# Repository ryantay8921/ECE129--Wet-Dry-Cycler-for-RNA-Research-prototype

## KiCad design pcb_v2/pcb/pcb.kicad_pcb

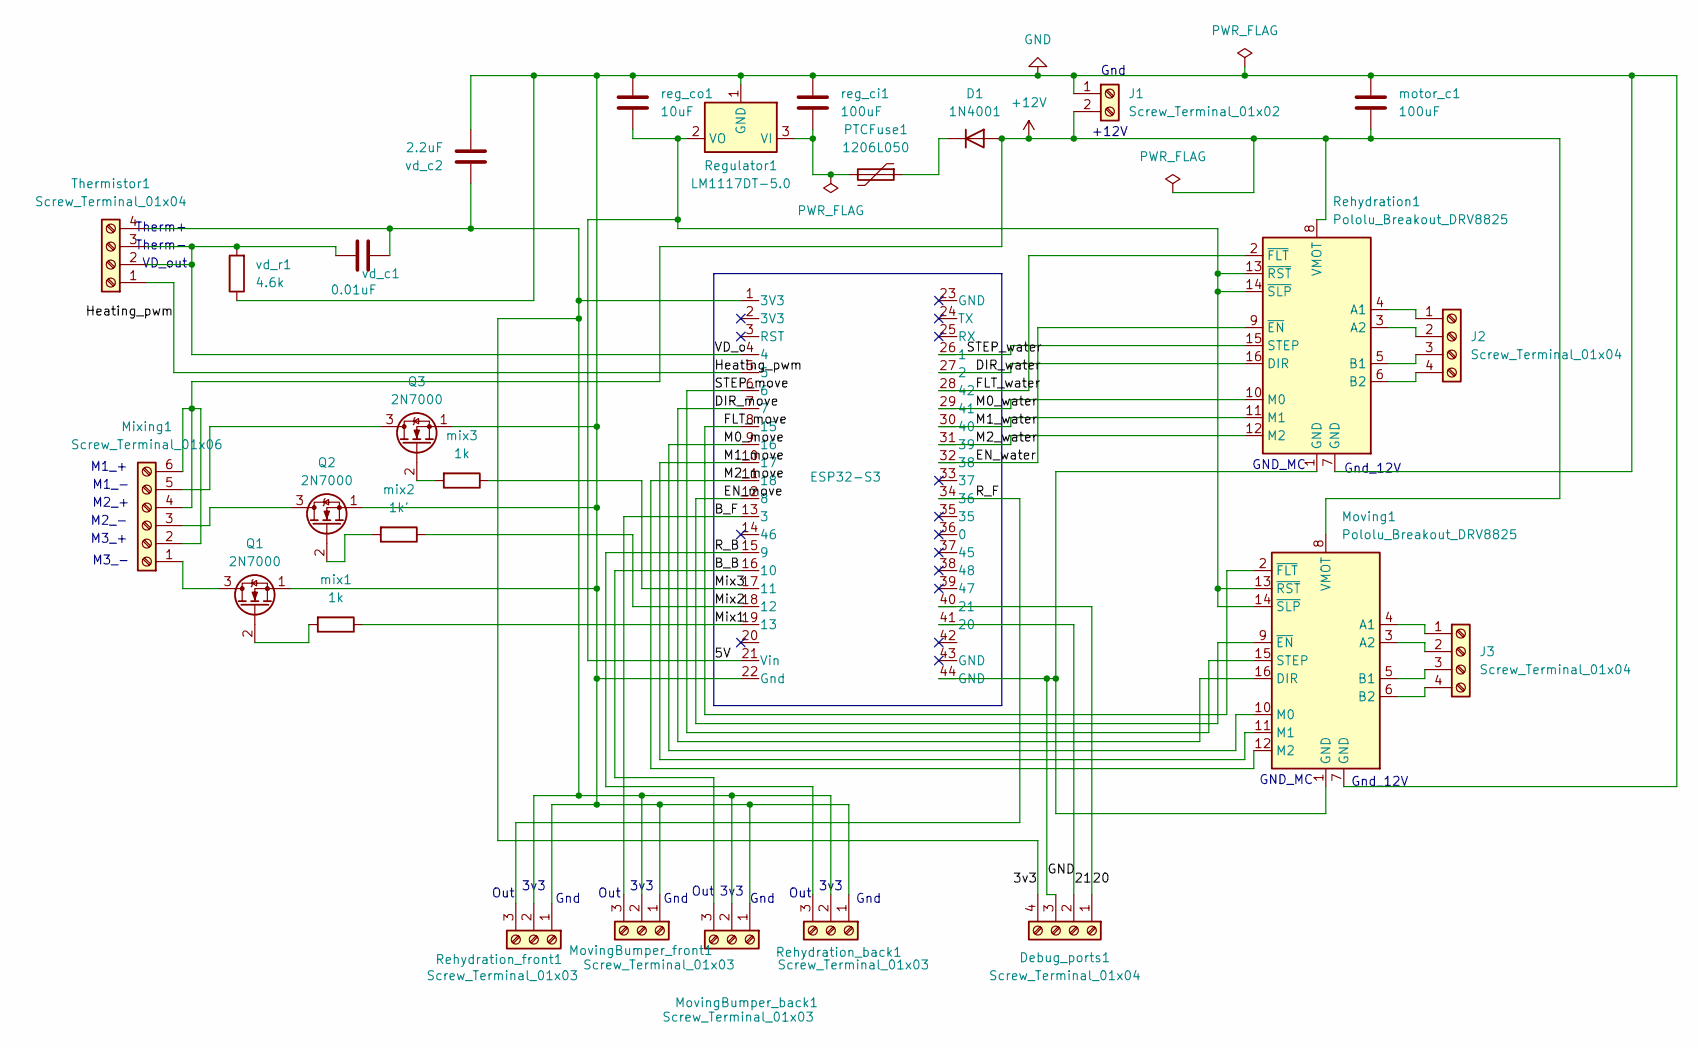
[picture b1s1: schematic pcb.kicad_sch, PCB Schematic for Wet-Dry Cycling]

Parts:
D1: 1N4001; D_DO-41_SOD81_P10.16mm_Horizontal
Debug_ports1: Screw_Terminal_01x04; TerminalBlock_MaiXu_MX126-5.0-04P_1x04_P5.00mm
ESP32-S3: ESP32_DevKitC_Header_Mount
J1: Screw_Terminal_01x02; TerminalBlock_MaiXu_MX126-5.0-02P_1x02_P5.00mm
J2, J3: Screw_Terminal_01x04; TerminalBlock_MaiXu_MX126-5.0-04P_1x04_P5.00mm
Mixing1: Screw_Terminal_01x06; TerminalBlock_MaiXu_MX126-5.0-06P_1x06_P5.00mm
Moving1: Pololu_Breakout_DRV8825; Pololu_Breakout-16_15.2x20.3mm
MovingBumper_back1: Screw_Terminal_01x03; TerminalBlock_MaiXu_MX126-5.0-03P_1x03_P5.00mm
MovingBumper_front1: Screw_Terminal_01x03; TerminalBlock_MaiXu_MX126-5.0-03P_1x03_P5.00mm
PTCFuse1: 1206L050; Fuse_1206_3216Metric_Pad1.42x1.75mm_HandSolder
Q1, Q2, Q3: 2N7000; TO-92_Inline
Regulator1: LM1117DT-5.0; TO-252-3_TabPin2
Rehydration1: Pololu_Breakout_DRV8825; Pololu_Breakout-16_15.2x20.3mm
Rehydration_back1: Screw_Terminal_01x03; TerminalBlock_MaiXu_MX126-5.0-03P_1x03_P5.00mm
Rehydration_front1: Screw_Terminal_01x03; TerminalBlock_MaiXu_MX126-5.0-03P_1x03_P5.00mm
Thermistor1: Screw_Terminal_01x04; TerminalBlock_MaiXu_MX126-5.0-04P_1x04_P5.00mm
mix1, mix3: 1k; R_0805_2012Metric_Pad1.20x1.40mm_HandSolder
mix2: 1k'; R_0805_2012Metric_Pad1.20x1.40mm_HandSolder
motor_c1: 100uF; C_0805_2012Metric_Pad1.18x1.45mm_HandSolder
reg_ci1: 100uF; C_0805_2012Metric_Pad1.18x1.45mm_HandSolder
reg_co1: 10uF; C_0805_2012Metric_Pad1.18x1.45mm_HandSolder
vd_c1: 0.01uF; C_0805_2012Metric_Pad1.18x1.45mm_HandSolder
vd_c2: 2.2uF; C_0805_2012Metric_Pad1.18x1.45mm_HandSolder
vd_r1: 4.6k; R_0805_2012Metric_Pad1.20x1.40mm_HandSolder

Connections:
+12V: D1.2 (A), J1.2, Mixing1.2, Mixing1.4, Mixing1.6, Moving1.8 (VMOT), Rehydration1.8 (VMOT), motor_c1.2
/3v3: Debug_ports1.4, ESP32-S3.1 (3V3), MovingBumper_back1.2, MovingBumper_front1.2, Rehydration_back1.2, Rehydration_front1.2, Thermistor1.4, vd_c1.2, vd_c2.1
/5V: ESP32-S3.21 (Vin), Moving1.13 (~RST), Moving1.14 (~SLP), Regulator1.2 (VO), Rehydration1.13 (~RST), Rehydration1.14 (~SLP), reg_co1.2
/20: Debug_ports1.1, ESP32-S3.40 (21)
/21: Debug_ports1.2, ESP32-S3.41 (20)
/B_B: ESP32-S3.16 (10), MovingBumper_back1.3
/B_F: ESP32-S3.13 (3), MovingBumper_front1.3
/DIR_move: ESP32-S3.7, Moving1.16 (DIR)
/DIR_water: ESP32-S3.27 (2), Rehydration1.16 (DIR)
/EN_move: ESP32-S3.12 (8), Moving1.9 (~EN)
/EN_water: ESP32-S3.32 (38), Rehydration1.9 (~EN)
/FLT_move: ESP32-S3.8 (15), Moving1.2 (~FLT)
/FLT_water: ESP32-S3.28 (42), Rehydration1.2 (~FLT)
/Heating_pwm: ESP32-S3.5, Thermistor1.1
/M0_move: ESP32-S3.9 (16), Moving1.10 (M0)
/M0_water: ESP32-S3.29 (41), Rehydration1.10 (M0)
/M1_move: ESP32-S3.10 (17), Moving1.11 (M1)
/M1_water: ESP32-S3.30 (40), Rehydration1.11 (M1)
/M2_move: ESP32-S3.11 (18), Moving1.12 (M2)
/M2_water: ESP32-S3.31 (39), Rehydration1.12 (M2)
/Mix1: ESP32-S3.19 (13), mix1.1
/Mix2: ESP32-S3.18 (12), mix2.1
/Mix3: ESP32-S3.17 (11), mix3.1
/R_B: ESP32-S3.15 (9), Rehydration_back1.3
/R_F: ESP32-S3.34 (36), Rehydration_front1.3
/STEP_move: ESP32-S3.6, Moving1.15 (STEP)
/STEP_water: ESP32-S3.26 (1), Rehydration1.15 (STEP)
/VD_o: ESP32-S3.4, Thermistor1.2, Thermistor1.3, vd_c1.1, vd_r1.2
GND: Debug_ports1.3, ESP32-S3.22 (Gnd), ESP32-S3.44 (GND), J1.1, Moving1.1 (GND), Moving1.7 (GND), MovingBumper_back1.1, MovingBumper_front1.1, Q1.1 (S), Q2.1 (S), Q3.1 (S), Regulator1.1 (GND), Rehydration1.1 (GND), Rehydration1.7 (GND), Rehydration_back1.1, Rehydration_front1.1, motor_c1.1, reg_ci1.1, reg_co1.1, vd_c2.2, vd_r1.1
unnamed: D1.1 (K), PTCFuse1.1
unnamed: J2.1, Rehydration1.4 (A1)
unnamed: J2.2, Rehydration1.3 (A2)
unnamed: J2.3, Rehydration1.5 (B1)
unnamed: J2.4, Rehydration1.6 (B2)
unnamed: J3.1, Moving1.4 (A1)
unnamed: J3.2, Moving1.3 (A2)
unnamed: J3.3, Moving1.5 (B1)
unnamed: J3.4, Moving1.6 (B2)
unnamed: Mixing1.1, Q1.3 (D)
unnamed: Mixing1.3, Q2.3 (D)
unnamed: Mixing1.5, Q3.3 (D)
unnamed: Q1.2 (G), mix1.2
unnamed: Q2.2 (G), mix2.2
unnamed: Q3.2 (G), mix3.2
unnamed: PTCFuse1.2, Regulator1.3 (VI), reg_ci1.2

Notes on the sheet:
Out
3v3
M2_-
Gnd_12V
Gnd
Therm-
+12V
GND_MC
M1_+
M2_+
M1_-
M3_-
M3_+
Therm+
VD_out

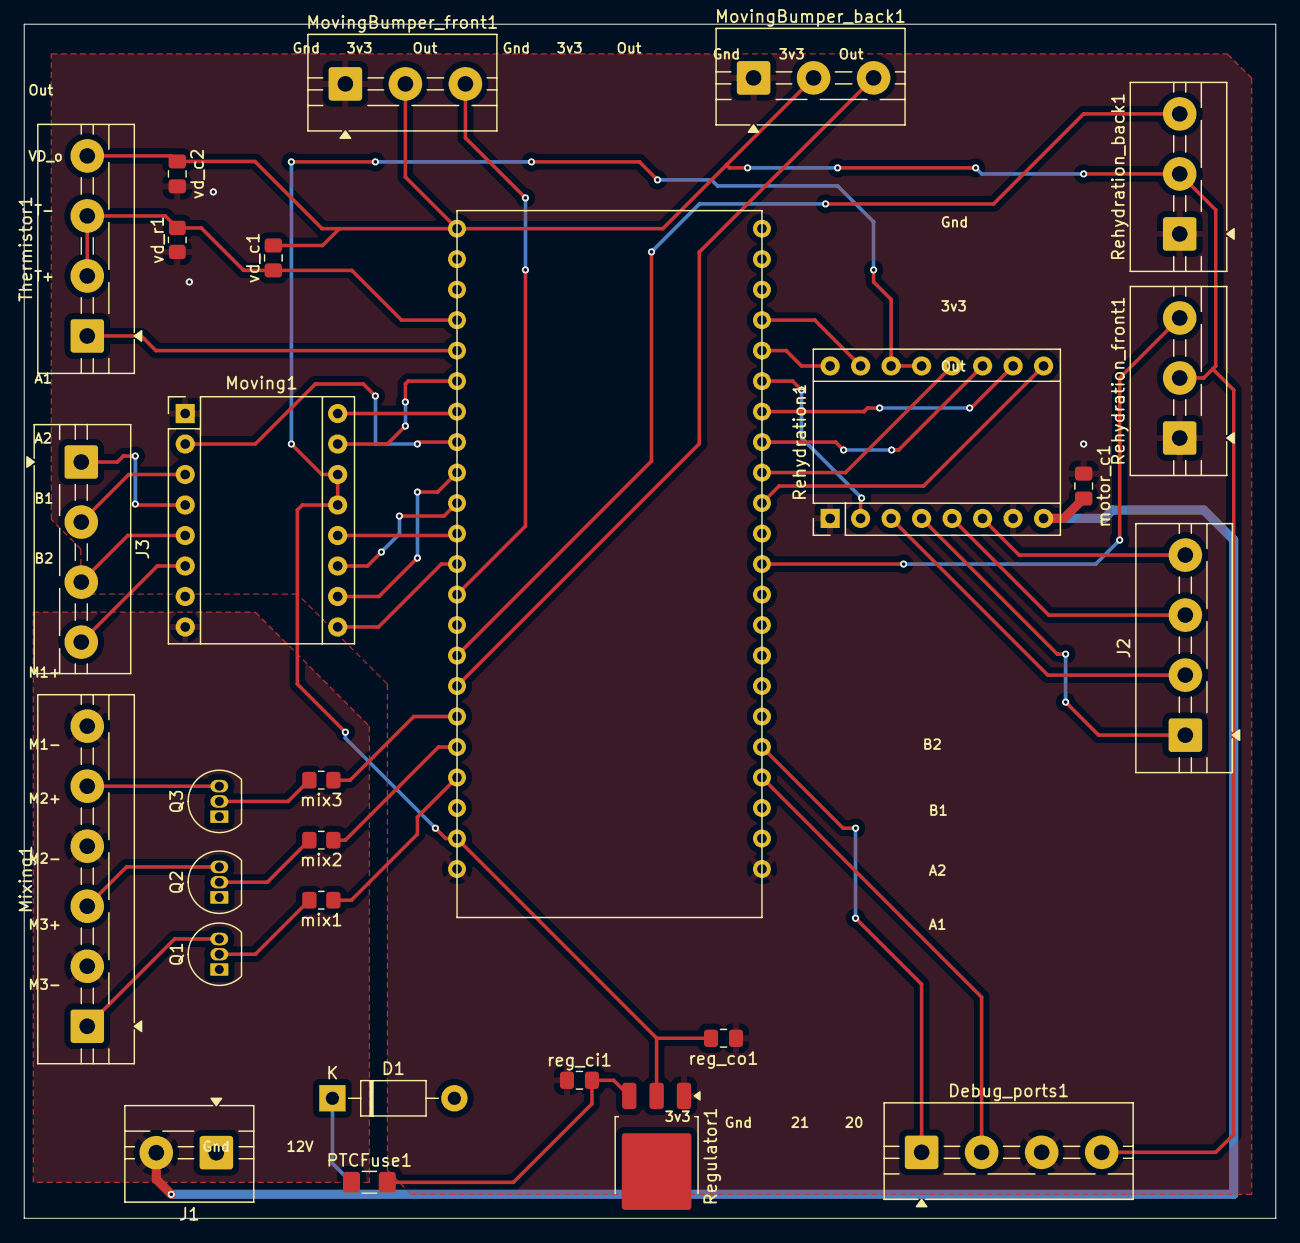
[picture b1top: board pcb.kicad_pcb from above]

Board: 2 copper layers, 104.2 x 99.5 mm, 28 parts (0 on the bottom side), 45 nets.

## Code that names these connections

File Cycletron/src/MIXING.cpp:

/**
 * @file    MIXING.cpp
 * @brief   DC Motor control module using GPIO pins (Arduino/ESP32 compatible).
 *
 * Provides initialization and control functions for mixing motors.
 *
 * @author  Rafael Delwart
 * @date    25 Feb 2025 adapted for ESP 13 May 2025
 */

#include <Arduino.h>
#include "MIXING.h"


// NOTE FOR VIKAS:
// PWM control of mixing motors, the speed is controlled by the power value
// 0 stops the motor, 255 is full speed. 
#define mixingMotorPower 177 // Default motor power (0-255), can be set from backend





#define mixingMotorPWMFrequency 500 // PWM frequency in Hz
#define TESTING_MIXING

// === CONFIG ===
#define MIX1_GPIO 11
#define MIX2_GPIO 12
#define MIX3_GPIO 13

// Define motor GPIOs and corresponding PWM channels
static const uint8_t motorPins[] = {MIX1_GPIO, MIX2_GPIO, MIX3_GPIO};
static const uint8_t motorChannels[] = {0, 1, 2}; // One channel per motor
static const int NUM_MOTORS = sizeof(motorPins) / sizeof(motorPins[0]);

// === API IMPLEMENTATION ===

/**
 * @brief Initializes all mixing motor GPIOs as PWM outputs (500Hz) and sets them LOW.
 */
void MIXING_Init() {
  for (int i = 0; i < NUM_MOTORS; i++) {
    pinMode(motorPins[i], OUTPUT);
    ledcSetup(motorChannels[i], mixingMotorPWMFrequency, 8);           // 500 Hz, 8-bit resolution
    ledcAttachPin(motorPins[i], motorChannels[i]); // Link pin to channel
    ledcWrite(motorChannels[i], 0);                // Motors off by default
  }
  Serial.println("[MIXING] All motors initialized and set to OFF");
}

/**
 * @brief Turns ON the motor connected to the given GPIO pin.
 * @param pin GPIO pin number
 */
void MIXING_Motor_OnPin(uint8_t pin)
{
  for (int i = 0; i < NUM_MOTORS; i++) {
    if (motorPins[i] == pin) {
      ledcWrite(motorChannels[i], mixingMotorPower);
      return;
    }
  }
}

/**
 * @brief Turns OFF the motor connected to the given GPIO pin.
 * @param pin GPIO pin number
 */
void MIXING_Motor_OffPin(uint8_t pin) {
  for (int i = 0; i < NUM_MOTORS; i++) {
    if (motorPins[i] == pin) {
      ledcWrite(motorChannels[i], 0);
      return;
    }
  }
}

/**
 * @brief Turns ON all defined motors.
 */
void MIXING_AllMotors_On() {
  for (int i = 0; i < NUM_MOTORS; i++) {
    ledcWrite(motorChannels[i], mixingMotorPower);
  }
}

/**
 * @brief Turns OFF all defined motors.
 */
void MIXING_AllMotors_Off() {
  for (int i = 0; i < NUM_MOTORS; i++) {
    ledcWrite(motorChannels[i], 0);
  }
}

// === TEST LOOP ===
// This section is for testing the mixing motors.
#ifdef TESTING_MIXING

void setup() {
  Serial.begin(115200);
  MIXING_Init();
}

void loop() {
  // Step through each motor
  for (int i = 0; i < NUM_MOTORS; i++) {
    Serial.printf("[TEST] Turning ON motor %d (GPIO %d)\n", i + 1, motorPins[i]);
    MIXING_Motor_OnPin(motorPins[i]);
    delay(10000); // ON for 10 seconds

    Serial.printf("[TEST] Turning OFF motor %d (GPIO %d)\n", i + 1, motorPins[i]);
    MIXING_Motor_OffPin(motorPins[i]);
    delay(3000);  // OFF for 3 seconds
  }

  // All motors ON
  Serial.println("[TEST] Turning ALL motors ON");
  MIXING_AllMotors_On();
  delay(20000);

  // All motors OFF
  Serial.println("[TEST] Turning ALL motors OFF");
  MIXING_AllMotors_Off();
  delay(5000);
}

#endif // TESTING_MIXING

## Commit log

2025-07-07 Added syringe refill popup message check
2025-07-07 Fixing pausing and percentage sent
2025-07-07 Fixing unknown state, and syringe bumper press
2025-07-07 Recovery fully working
2025-07-08 added syringe status stuff
2025-07-08 total duration in log cycle
2025-07-08 log cycle now goes to downloads. and pops up on cycle end
2025-07-09 adding lab wifi and ip
2025-07-09 adding lab wifi
2025-07-10 fixed multiple log downloads
2025-07-11 Switching order of states and new code that should be tested in (DRV, handle, REHYDRATION and main)
2025-07-11 Added a countdown timer to front end
2025-07-14 small test changes to the code for cycle inversion
2025-07-14 timer pause resume loses a couple seconds, but works good enough
2025-07-15 Adding changes in mixing in order to be able to control the speed of the mixing motors with PWM. (Frequency of PWM set low(500Hz) to protect the mosfet controlling the motors) branch 'main' into LabB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
2026-04-23 final report
